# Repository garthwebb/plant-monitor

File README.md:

# plant-monitor

Code for the remote moisture sensing plant monitor with a moisture sensor as well as a temperature sensor, controlled by an AVR ATTiny device.  The plant monitor runs off a rechargable LiPo battery and wakes up every ~10 min to send moisture, temperature and battery level data back to a central receiver (a RaspberryPi).  The receiver is plugged in and connected to a WiFi network.  It logs each data event to InfluxDB, which could be hosted on the receiving RaspberryPi or somewhere else.

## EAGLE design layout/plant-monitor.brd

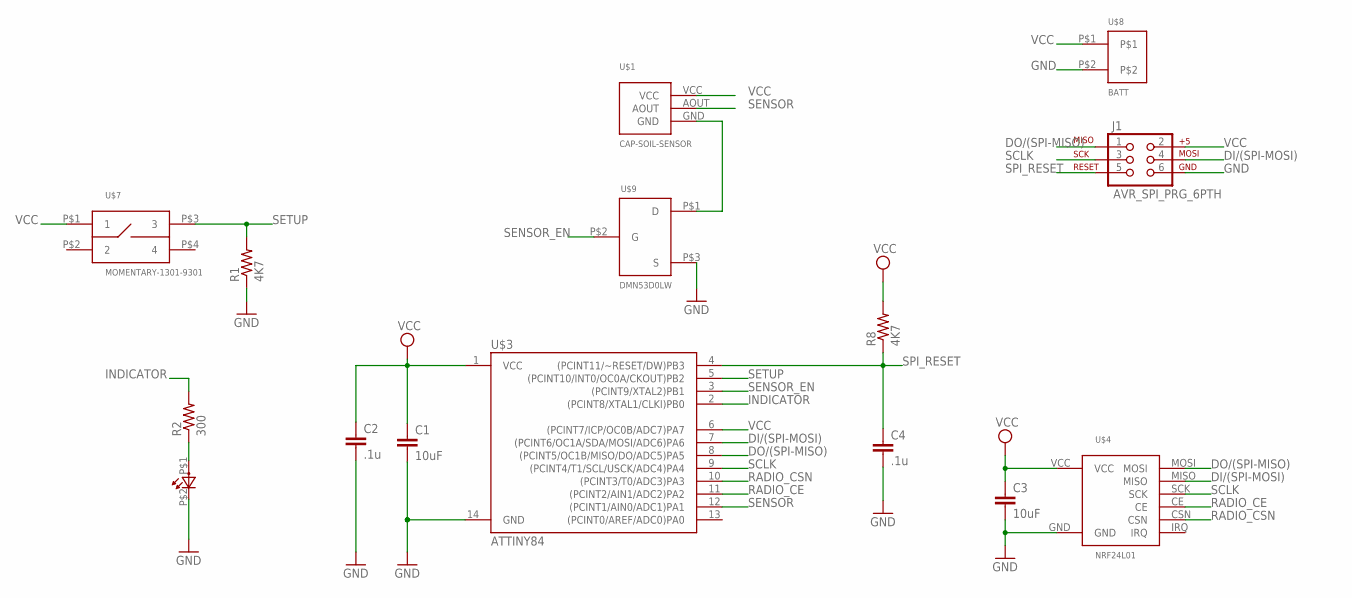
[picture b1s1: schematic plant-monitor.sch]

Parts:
C1, C3: 10uF; 1206
C2, C4: .1u; 0805
J1: AVR_SPI_PRG_6PTH; 2X3
R1, R8: 4K7; 0805
R2: 300; 0805
U$1: CAP-SOIL-SENSOR
U$3: ATTINY84; SO14
U$4: NRF24L01
U$6: LED; 0805
U$7: MOMENTARY-1301-9301; MOMENTARY-1301
U$8: BATT; JST-PH-2
U$9: DMN53D0LW; SOT-323

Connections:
DI/(SPI-MOSI): J1.4, U$3.7 ((PCINT6/OC1A/SDA/MOSI/ADC6)PA6), U$4.MISO
DO/(SPI-MISO): J1.1, U$3.8 ((PCINT5/OC1B/MISO/DO/ADC5)PA5), U$4.MOSI
GND: C1.2, C2.2, C3.2, C4.2, J1.6, R1.1, U$3.14 (GND), U$4.GND, U$6.P$2 (C), U$8.P$2, U$9.P$3 (S)
INDICATOR: R2.2, U$3.2 ((PCINT8/XTAL1/CLKI)PB0)
unnamed: R2.1, U$6.P$1 (A)
unnamed: U$1.GND, U$9.P$1 (D)
RADIO_CE: U$3.11 ((PCINT2/AIN1/ADC2)PA2), U$4.CE
RADIO_CSN: U$3.10 ((PCINT3/T0/ADC3)PA3), U$4.CSN
SCLK: J1.3, U$3.9 ((PCINT4/T1/SCL/USCK/ADC4)PA4), U$4.SCK
SENSOR: U$1.AOUT, U$3.12 ((PCINT1/AIN0/ADC1)PA1)
SENSOR_EN: U$3.3 ((PCINT9/XTAL2)PB1), U$9.P$2 (G)
SETUP: R1.2, U$3.5 ((PCINT10/INT0/OC0A/CKOUT)PB2), U$7.P$3 (3)
SPI_RESET: C4.1, J1.5, R8.1, U$3.4 ((PCINT11/~RESET/DW)PB3)
VCC: C1.1, C2.1, C3.1, J1.2, R8.2, U$1.VCC, U$3.1 (VCC), U$3.6 ((PCINT7/ICP/OC0B/ADC7)PA7), U$4.VCC, U$7.P$1 (1), U$8.P$1

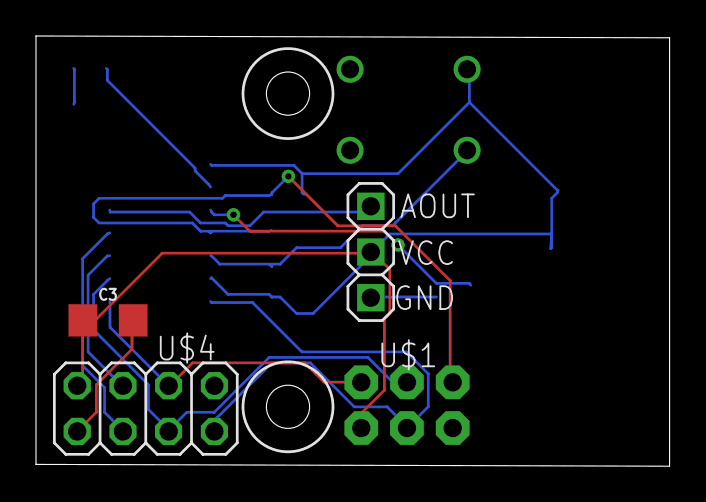
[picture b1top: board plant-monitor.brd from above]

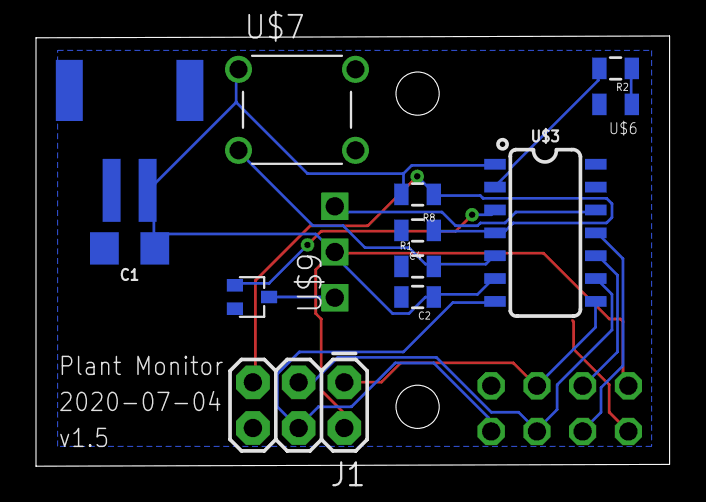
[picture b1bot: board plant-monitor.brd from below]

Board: 2 copper layers, 35.2 x 23.9 mm, 15 parts (12 on the bottom side), 14 nets.

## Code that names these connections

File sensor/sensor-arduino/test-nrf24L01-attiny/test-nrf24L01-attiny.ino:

/*
    ATtiny24/44/84 Pin map with CE_PIN 8 and CSN_PIN 7
  Schematic provided and successfully tested by Carmine Pastore (https://github.com/Carminepz)
                                  +-\/-+
    nRF24L01  VCC, pin2 --- VCC  1|o   |14 GND --- nRF24L01  GND, pin1
                            PB0  2|    |13 AREF
                            PB1  3|    |12 PA1
                            PB3  4|    |11 PA2 --- nRF24L01   CE, pin3
                            PB2  5|    |10 PA3 --- nRF24L01  CSN, pin4
                            PA7  6|    |9  PA4 --- nRF24L01  SCK, pin5
    nRF24L01 MOSI, pin7 --- PA6  7|    |8  PA5 --- nRF24L01 MISO, pin6
                                  +----+
*/

#include <avr/sleep.h>
#include <avr/wdt.h>

#include "RF24.h"

/****************** User Config ***************************/
// Set this radio as radio number 0 or 1
bool radioNumber = 0;

#define MOISTURE_ADC 0

#define SELF_ID 0xfeed

#define HOST_RADIO_ADDR (byte *) "1Node"
#define SELF_RADIO_ADDR (byte *) "2Node"

// CE and CSN are configurable, specified values for ATtiny84 as connected above
#define RAIDIO_CE 2
#define RAIDIO_CSN 3

#define COMMAND_STATUS 0x01

RF24 radio(RAIDIO_CE, RAIDIO_CSN);

uint32_t status_cycles = 0;

void setup() {
  pinMode(MOISTURE_ADC, INPUT);

  //blinkLed();
  //blinkLed();
  
  initRadio();
}

/*
void blinkLed(void) {
  digitalWrite(LED_PIN, HIGH);
  delay(500);
  digitalWrite(LED_PIN, LOW);
  delay(500);
}
*/

void initRadio() {
  // Setup and configure rf radio
  radio.begin();
  radio.setPALevel(RF24_PA_LOW);
  radio.setAutoAck(1);

  // Max delay between retries & number of retries
  radio.setRetries(15, 15);

  // Open a writing and reading pipe on each radio, with opposite addresses
  radio.openWritingPipe(HOST_RADIO_ADDR);
  radio.openReadingPipe(1, SELF_RADIO_ADDR);

  // Start listening
  radio.startListening();
}

uint8_t getMoistureValue(void) {
  return analogRead(MOISTURE_ADC);
}

int radioWriteBytes(uint8_t* buf, uint8_t len) {
  int success = 1;
  
  // First, stop listening so we can talk.
  radio.stopListening();         

  if (!radio.write(buf, len*sizeof(uint8_t))) {
    success = 0;
  }

  // Now, continue listening
  radio.startListening();
  return success;
}

int sendStatus(void) {
  uint32_t payload[4];
  payload[0] = COMMAND_STATUS;
  payload[1] = SELF_ID;
  payload[2] = status_cycles;
  payload[3] = getMoistureValue();

  bool success = true;
  
  radio.stopListening();
  if (!radio.write(&payload, sizeof(payload))) {
    success = false;
  }
  radio.startListening();

  // Increment every time we send as a proxy for power
  status_cycles++;
}

void loop(void) {
  //blinkLed();
  unsigned long start_time = micros();

  sendStatus();

  // Set up a timeout period, get the current microseconds
  unsigned long started_waiting_at = micros();
  // Set up a variable to indicate if a response was received or not
  boolean timeout = false;

  // While nothing is received
  while ( !radio.available() ) {
    // If waited longer than 200ms, indicate timeout and exit while loop
    if (micros() - started_waiting_at > 2000000) {
      timeout = true;
      break;
    }      
  }
  
  unsigned long got_time = 0;
  if (!timeout) {
    // Grab the response, compare, and send to debugging spew
    radio.read( &got_time, sizeof(unsigned long) );
  }

  // Try again 1m later
  delay(1000);
}

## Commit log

2020-02-08 Initial check in
2020-05-17 Updated design to address problems in v1.3 board, notably ower switching added for soil sensor
2020-07-04 Add in a vcc measurement so we can do away with the 5v regulator on the board and run everying directly off battery.
    The moisture sensor is supposed to regulate to 3.3 v so all ADC readings should be relative to that.
2020-07-04 Ignore eagle lock files and add the last two layouts
2020-07-04 Go back to default power value
2020-07-06 Updated board design that removes the voltage regulator. The moisture meter does this and its not necessary
2020-07-06 Updated code to send battery level in the status message
2020-07-14 Save an image of this version so I can refer to it later without having bring back an old version, then load it in eagle.
2020-07-21 Updated to have working makefile and compiling collector code.
2020-08-12 Updated sensor code can't remember all the changes plz look at diff kthxbai
2020-08-12 Fix the Makefile so it produces a working binary
    I blindly copied the bits out of the RF24 library Makefile and generated Makefile.inc.
    Most of that stuff was just for buildng the library. Once you ./configure and install that
    the Makefile to build code that uses it is much simplier
2020-08-12 Simplified CMakelists, updated collector to respond to new queries from the sensor, added an echo program

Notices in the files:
parts and their libraries:
SparkFun-Connectors: Licensing: CC v3.0 Share-Alike You are welcome to use this library for commercial purposes.
SparkFun-Capacitors: Licensing: Creative Commons ShareAlike 4.0 International - https://creativecommons.org/licenses/by-sa/4.0
